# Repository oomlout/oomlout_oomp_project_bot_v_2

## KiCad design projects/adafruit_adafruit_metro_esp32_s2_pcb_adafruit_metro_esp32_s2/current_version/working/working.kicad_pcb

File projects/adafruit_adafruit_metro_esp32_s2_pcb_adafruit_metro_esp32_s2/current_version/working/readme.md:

# adafruit_metro_esp32_s2_pcb
 
## summary 
* id: adafruit_adafruit_metro_esp32_s2_pcb_adafruit_metro_esp32_s2
* user: adafruit
* name: adafruit_metro_esp32_s2_pcb
* board: adafruit_metro_esp32_s2
* repo: https://github.com/adafruit/Adafruit-Metro-ESP32-S2-PCB

* src_file_repo_sch: 
* src_file_repo_sch_link: https://github.com/adafruit/Adafruit-Metro-ESP32-S2-PCB/tree/master/
* full details link: https://github.com/oomlout/oomlout_oomp_project_bot_v_2/tree/main/projects/adafruit_adafruit_metro_esp32_s2_pcb_adafruit_metro_esp32_s2/current_version/working  

## schematic  
  
[schematic (pdf)](working_schematic.pdf) 

## pcb  

[board (pdf)](working.pdf)  

## working_bom
| Id | Designator | Footprint | Quantity | Designation | Supplier and ref |  | None | 
| --- | --- | --- | --- | --- | --- | --- | --- | 
| 1 | IOL0,POWER0 | 1X08_OVALWAVE | 2 | 20610 |  |  | [''] | 
| 2 | @HOLE3,@HOLE0,@HOLE2,@HOLE1 |  | 4 |  |  |  | [''] | 
| 3 | C4,C13,C7,C10,C18,C17,C11,C8 | 0805-NO | 8 | 10ÂµF |  |  | [''] | 
| 4 | C1,C3 | 0805-NO | 2 | 10uF |  |  | [''] | 
| 5 | U3 | MODULE_ESP32-S2-WROVER | 1 | ESP32-S2-WROVER |  |  | [''] | 
| 6 | D1,D4 | SOD-123 | 2 | MBR540 |  |  | [''] | 
| 7 | CHG1 | CHIPLED_0603_NOOUTLINE | 1 | ORANGE |  |  | [''] | 
| 8 | R15,R12,R16 | 0603-NO | 3 | 100K |  |  | [''] | 
| 9 | R2,R9,R6 | 0603-NO | 3 | 10K |  |  | [''] | 
| 10 | X5 | DCJACK_2MM_PTH | 1 | 2.1mm |  |  | [''] | 
| 11 | C5,C2,C12,C15 | 0603-NO | 4 | 0.1uF |  |  | [''] | 
| 12 | U$15 | PCBFEAT-REV-040 | 1 |  |  |  | [''] | 
| 13 | ON0 | CHIPLED_0603_NOOUTLINE | 1 | GREEN |  |  | [''] | 
| 14 | Q2,Q1 | SOT23-R | 2 | DMG3415U-7 |  |  | [''] | 
| 15 | X4 | USB_C_CUSB31-CFM2AX-01-X | 1 | USB C |  |  | [''] | 
| 16 | PC2 | PANASONIC_D | 1 | 47uF+/6.3V+ |  |  | [''] | 
| 17 | C14,C6 | 0603-NO | 2 | 1uF |  |  | [''] | 
| 18 | SW4 | SPDT_SMT_SSSS811101 | 1 | SPDT R/A |  |  | [''] | 
| 19 | SW1,SW3 | SPST_TACTILE_RA | 2 | RA_TACT |  |  | [''] | 
| 20 | FD2,FD1,FD3 | FIDUCIAL_1MM | 3 | FIDUCIAL_1MM |  |  | [''] | 
| 21 | LED1 | LED3535 | 1 | WS2812B3535 |  |  | [''] | 
| 22 | CONN1 | JST_SH4 | 1 | STEMMA_I2C_QT |  |  | [''] | 
| 23 | U1 | SOT223-R | 1 | NCP1117ST50T3G |  |  | [''] | 
| 24 | X1 | JSTPH2_BATT | 1 | JSTPH |  |  | [''] | 
| 25 | U$52 | ESP32S2_TOP | 1 |  |  |  | [''] | 
| 26 | U4 | SOT23-5 | 1 | AP2112(3.3V) |  |  | [''] | 
| 27 | IOH0 | 1X10_OVALWAVE | 1 | 20611 |  |  | [''] | 
| 28 | ICSP0 | 2X03_ROUND_70MIL | 1 | 3x2 M |  |  | [''] | 
| 29 | R14 | 0603-NO | 1 | 100k |  |  | [''] | 
| 30 | R3,R8 | 0603-NO | 2 | 5.1K |  |  | [''] | 
| 31 | X2 | 2X05_1.27MM_BOX_POSTS | 1 | 4u20317 |  |  | [''] | 
| 32 | U2 | SOT23-5 | 1 | MCP73831T-2ACI/OT |  |  | [''] | 
| 33 | L0 | CHIPLED_0603_NOOUTLINE | 1 | RED |  |  | [''] | 
| 34 | JP2 | 1X02_ROUND | 1 | UART |  |  | [''] | 
| 35 | PC1 | PANASONIC_D | 1 | 47uF/25V |  |  | [''] | 
| 36 | F2 | 1206 | 1 | 500mA |  |  | [''] | 
| 37 | R17 | 0603-NO | 1 | 1Meg |  |  | [''] | 
| 38 | R4 | 0603-NO | 1 | 2.2K |  |  | [''] | 
| 39 | AD0 | 1X06_OVALWAVE | 1 | 20609 |  |  | [''] | 
| 40 | R1 | RESPACK_4X0603 | 1 | 10K |  |  | [''] | 
| 41 | IC2 | WDFN8_3X4_0.65 | 1 | LC709203F |  |  | [''] | 
| 42 | U$53 | ESP32S2_BOT | 1 |  |  |  | [''] | 
| 43 | SJ1 | SOLDERJUMPER_CLOSEDWIRE | 1 |  |  |  | [''] | 
| 44 | TP1 | TESTPOINT_ROUND_1.5MM_NO | 1 |  |  |  | [''] | 

## bom_schematic
| Ref | Qnty | Value | Cmp name | Footprint | Description | Vendor | DNP | 
| --- | --- | --- | --- | --- | --- | --- | --- | 
| AD0 | 1 | 20609 | HEADER-1X6OVALWAVE | working:1X06_OVALWAVE |  |  |  | 
| C1, C3 | 2 | 10uF | CAP_CERAMIC0805-NOOUTLINE | working:0805-NO |  |  |  | 
| C2, C5, C12, C15 | 4 | 0.1uF | CAP_CERAMIC0603_NO | working:0603-NO |  |  |  | 
| C4, C7, C8, C10, C11, C13, C17, C18 | 8 | 10ÂµF | CAP_CERAMIC0805-NOOUTLINE | working:0805-NO |  |  |  | 
| C6, C14 | 2 | 1uF | CAP_CERAMIC0603_NO | working:0603-NO |  |  |  | 
| CHG1 | 1 | ORANGE | LED0603_NOOUTLINE | working:CHIPLED_0603_NOOUTLINE |  |  |  | 
| CONN1 | 1 | STEMMA_I2C_QT | STEMMA_I2C_QT | working:JST_SH4 |  |  |  | 
| D1, D4 | 2 | MBR540 | DIODE-SCHOTTKYSOD-123 | working:SOD-123 |  |  |  | 
| F2 | 1 | 500mA | PTC1206 | working:1206 |  |  |  | 
| FD1, FD2, FD3 | 3 | FIDUCIAL_1MM | FIDUCIAL_1MM | working:FIDUCIAL_1MM |  |  |  | 
| IC2 | 1 | LC709203F | LC709203F | working:WDFN8_3X4_0.65 |  |  |  | 
| ICSP0 | 1 | 3x2 M | HEADER-2X3 | working:2X03_ROUND_70MIL |  |  |  | 
| IOH0 | 1 | 20611 | HEADER-1X10OVALWAVE | working:1X10_OVALWAVE |  |  |  | 
| IOL0 | 1 | 20610 | HEADER-1X8OVALWAVE | working:1X08_OVALWAVE |  |  |  | 
| JP2 | 1 | UART | HEADER-1X2ROUND | working:1X02_ROUND |  |  |  | 
| L0 | 1 | RED | LED0603_NOOUTLINE | working:CHIPLED_0603_NOOUTLINE |  |  |  | 
| LED1 | 1 | WS2812B3535 | WS2812B3535 | working:LED3535 |  |  |  | 
| ON0 | 1 | GREEN | LED0603_NOOUTLINE | working:CHIPLED_0603_NOOUTLINE |  |  |  | 
| PC1 | 1 | 47uF/25V | CAP_ELECTROLYTICPANASONIC_D | working:PANASONIC_D |  |  |  | 
| PC2 | 1 | 47uF+/6.3V+ | CAP_ELECTROLYTICPANASONIC_D | working:PANASONIC_D |  |  |  | 
| POWER0 | 1 | 20610 | HEADER-1X8OVALWAVE | working:1X08_OVALWAVE |  |  |  | 
| Q1, Q2 | 2 | DMG3415U-7 | MOSFET-P | working:SOT23-R |  |  |  | 
| R1 | 1 | 10K | RESISTOR_4PACK | working:RESPACK_4X0603 |  |  |  | 
| R2, R6, R9 | 3 | 10K | RESISTOR_0603_NOOUT | working:0603-NO |  |  |  | 
| R3, R8 | 2 | 5.1K | RESISTOR_0603_NOOUT | working:0603-NO |  |  |  | 
| R4 | 1 | 2.2K | RESISTOR_0603_NOOUT | working:0603-NO |  |  |  | 
| R12, R15, R16 | 3 | 100K | RESISTOR_0603_NOOUT | working:0603-NO |  |  |  | 
| R14 | 1 | 100k | RESISTOR_0603_NOOUT | working:0603-NO |  |  |  | 
| R17 | 1 | 1Meg | RESISTOR_0603_NOOUT | working:0603-NO |  |  |  | 
| SJ1 | 1 | SOLDERJUMPER_CLOSED | SOLDERJUMPER_CLOSED | working:SOLDERJUMPER_CLOSEDWIRE |  |  |  | 
| SW1, SW3 | 2 | RA_TACT | SWITCH_SPST_TACT_RA | working:SPST_TACTILE_RA |  |  |  | 
| SW4 | 1 | SPDT R/A | SWITCH_SPDT | working:SPDT_SMT_SSSS811101 |  |  |  | 
| TP1 | 1 | TESTPOINTROUND1.5MMNO | TESTPOINTROUND1.5MMNO | working:TESTPOINT_ROUND_1.5MM_NO |  |  |  | 
| U1 | 1 | NCP1117ST50T3G | LM1117SOT223-REFLOW | working:SOT223-R |  |  |  | 
| U2 | 1 | MCP73831T-2ACI/OT | MCP73831/2 | working:SOT23-5 |  |  |  | 
| U3 | 1 | ESP32-S2-WROVER | ESP32-S2-WROVER | working:MODULE_ESP32-S2-WROVER |  |  |  | 
| U4 | 1 | AP2112(3.3V) | VREG_SOT23-5 | working:SOT23-5 |  |  |  | 
| X1 | 1 | JSTPH | CON_JST_PH_2PIN_BATT | working:JSTPH2_BATT |  |  |  | 
| X2 | 1 | 4u20317 | JTAG-CORTEXBOXPOSTS | working:2X05_1.27MM_BOX_POSTS |  |  |  | 
| X4 | 1 | USB C | USB_C | working:USB_C_CUSB31-CFM2AX-01-X |  |  |  | 
| X5 | 1 | 2.1mm | DCBARRELPTH | working:DCJACK_2MM_PTH |  |  |  |

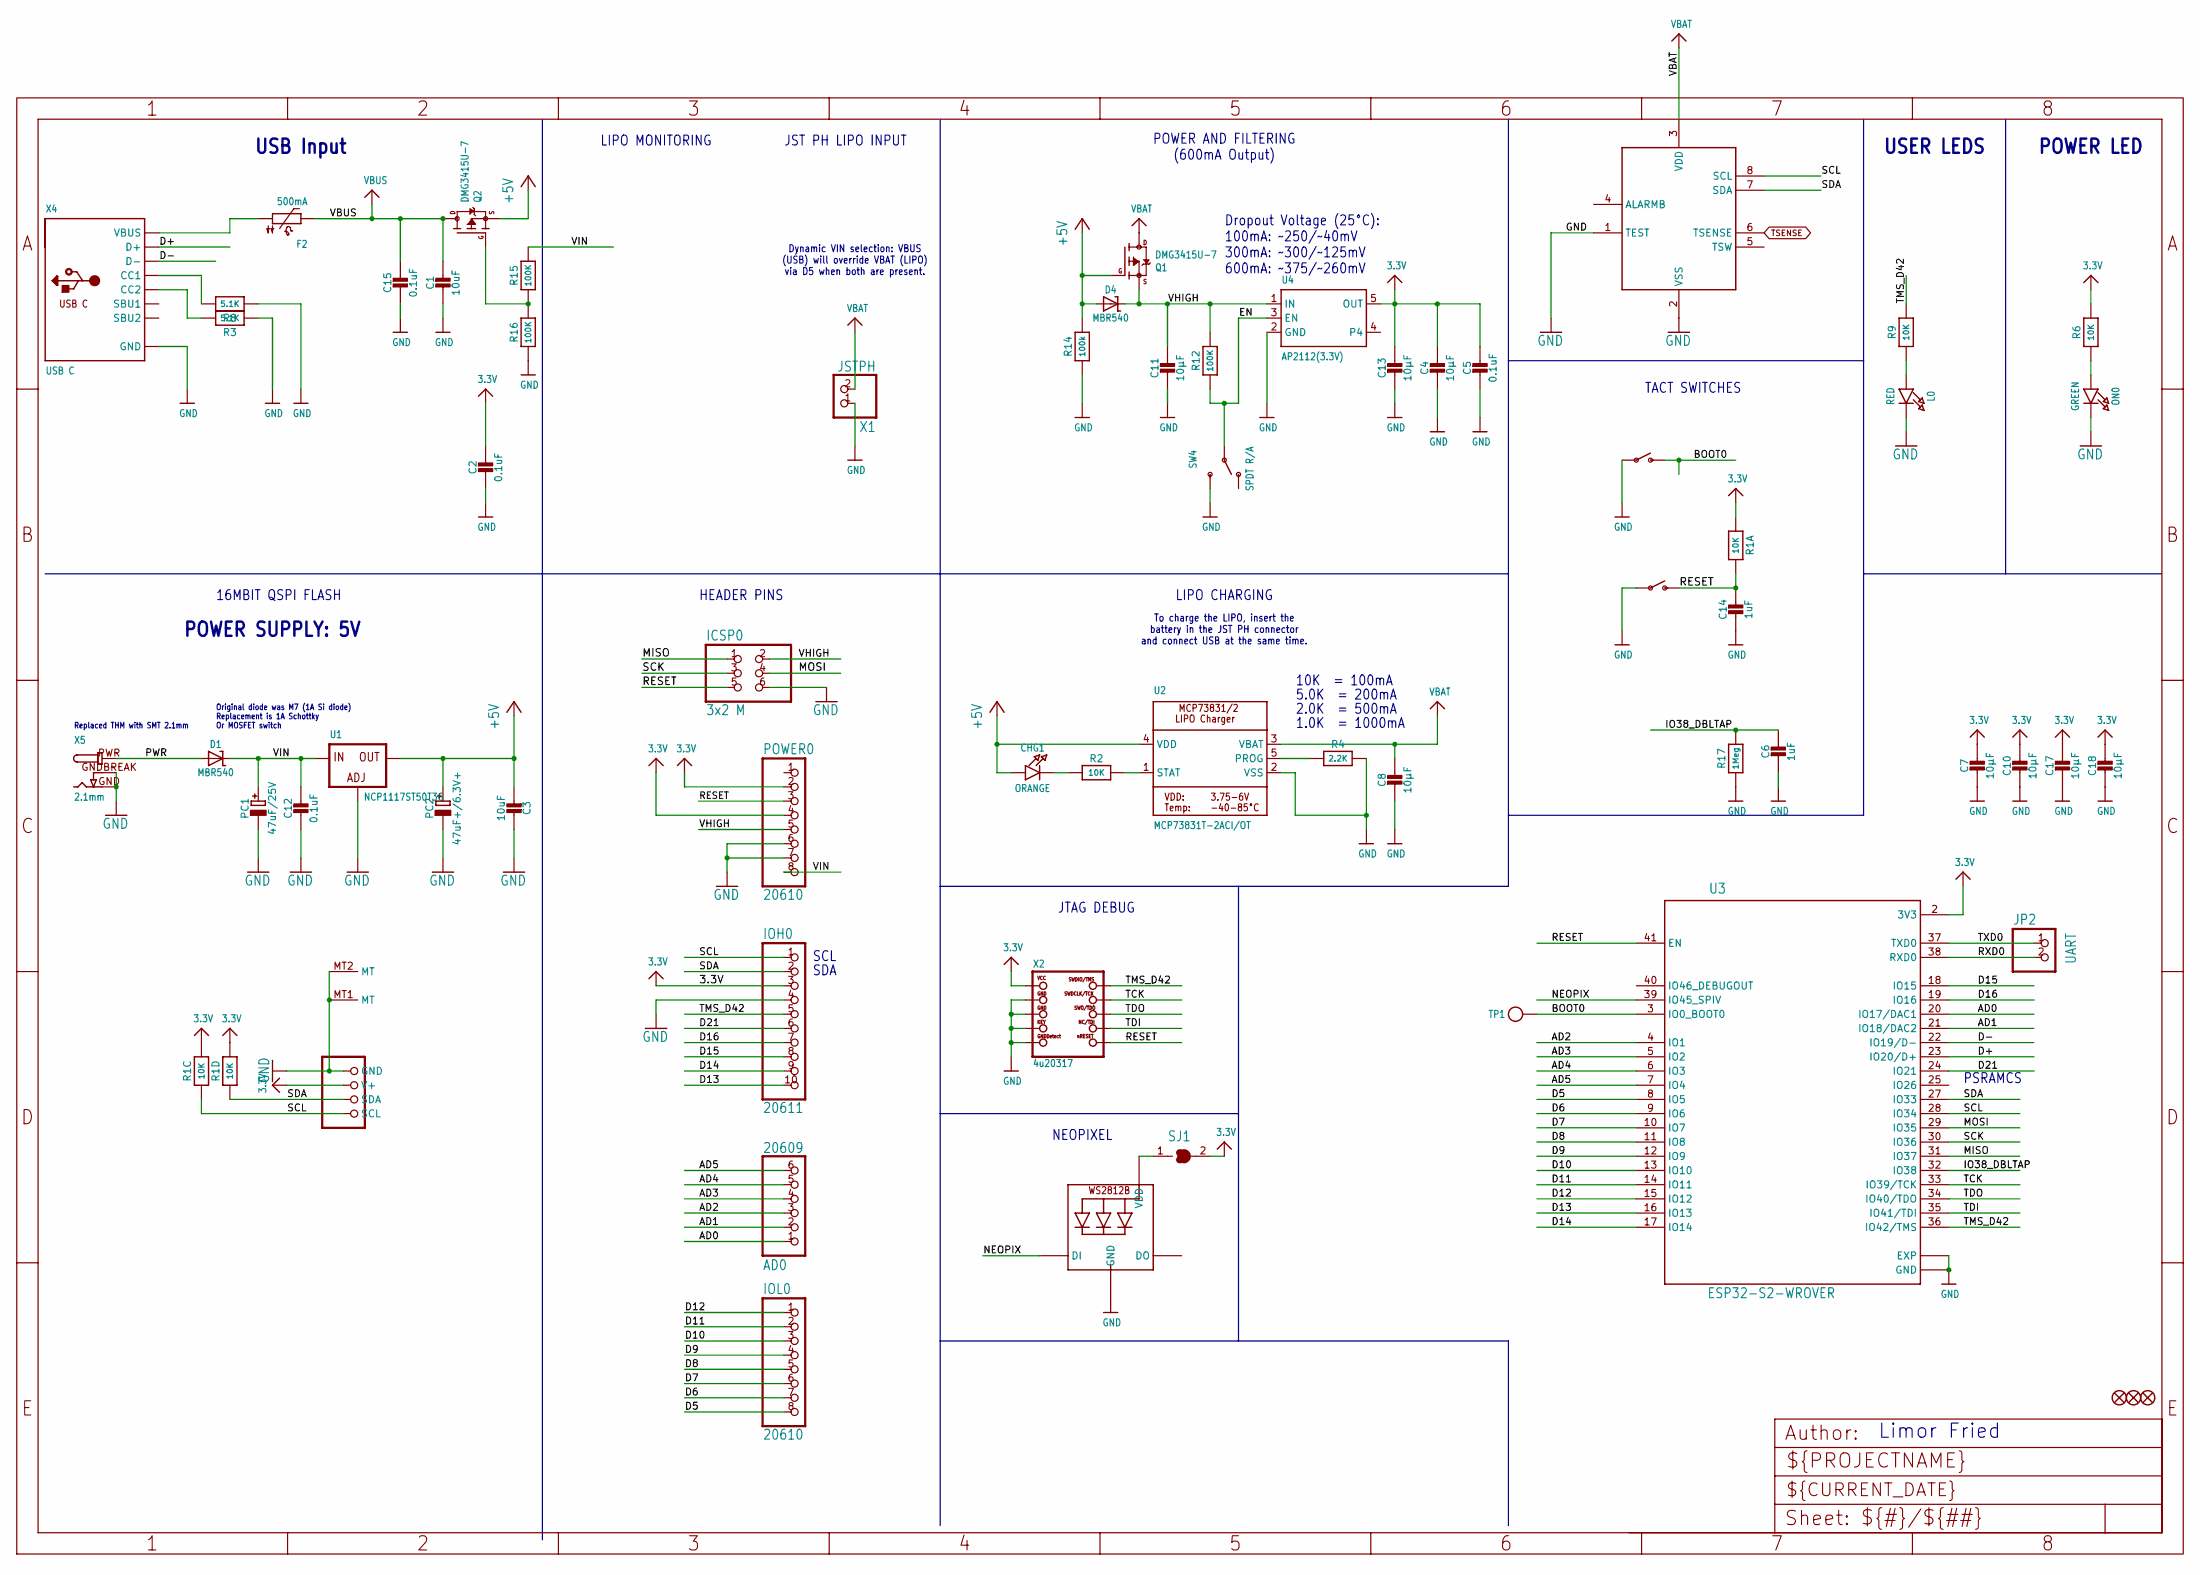
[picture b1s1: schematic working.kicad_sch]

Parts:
AD0: 20609; 1X06_OVALWAVE
C1, C3: 10uF; 0805-NO
C2, C5, C12, C15: 0.1uF; 0603-NO
C4, C7, C8, C10, C11, C13, C17, C18: 10µF; 0805-NO
C6, C14: 1uF; 0603-NO
CHG1: ORANGE; CHIPLED_0603_NOOUTLINE
CONN1: STEMMA_I2C_QT; JST_SH4
D1, D4: MBR540; SOD-123
F2: 500mA; 1206
FD1, FD2, FD3: FIDUCIAL_1MM
IC2: LC709203F; WDFN8_3X4_0.65
ICSP0: 3x2 M; 2X03_ROUND_70MIL
IOH0: 20611; 1X10_OVALWAVE
IOL0: 20610; 1X08_OVALWAVE
JP2: UART; 1X02_ROUND
L0: RED; CHIPLED_0603_NOOUTLINE
LED1: WS2812B3535; LED3535
ON0: GREEN; CHIPLED_0603_NOOUTLINE
PC1: 47uF/25V; PANASONIC_D
PC2: 47uF+/6.3V+; PANASONIC_D
POWER0: 20610; 1X08_OVALWAVE
Q1, Q2: DMG3415U-7; SOT23-R
R1: 10K; RESPACK_4X0603
R2, R6, R9: 10K; 0603-NO
R3, R8: 5.1K; 0603-NO
R4: 2.2K; 0603-NO
R12, R15, R16: 100K; 0603-NO
R14: 100k; 0603-NO
R17: 1Meg; 0603-NO
SJ1: SOLDERJUMPER_CLOSED; SOLDERJUMPER_CLOSEDWIRE
SW1, SW3: RA_TACT; SPST_TACTILE_RA
SW4: SPDT R/A; SPDT_SMT_SSSS811101
TP1: TESTPOINTROUND1.5MMNO; TESTPOINT_ROUND_1.5MM_NO
U1: NCP1117ST50T3G; SOT223-R
U2: MCP73831T-2ACI/OT; SOT23-5
U3: ESP32-S2-WROVER; MODULE_ESP32-S2-WROVER
U4: AP2112(3.3V); SOT23-5
X1: JSTPH; JSTPH2_BATT
X2: 4u20317; 2X05_1.27MM_BOX_POSTS
X4: USB C; USB_C_CUSB31-CFM2AX-01-X
X5: 2.1mm; DCJACK_2MM_PTH

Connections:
3.3V: C2.1, C4.1, C5.1, C7.1, C10.1, C13.1, C17.1, C18.1, CONN1.2 (V+), IOH0.3, POWER0.2, POWER0.4, R1.1, R1.5 (2), R1.6 (2), R6.2, SJ1.2, U3.2 (3V3), U4.5 (OUT), X2.1 (VCC)
+5V: C3.2, CHG1.A, D4.A, PC2.+, Q1.1 (G), Q2.2 (S), R14.2, U1.2 (OUT), U1.4 (OUT), U2.4 (VDD)
AD0: AD0.1, U3.20 (IO17/DAC1)
AD1: AD0.2, U3.21 (IO18/DAC2)
AD2: AD0.3, U3.4 (IO1)
AD3: AD0.4, U3.5 (IO2)
AD4: AD0.5, U3.6 (IO3)
AD5: AD0.6, U3.7 (IO4)
BOOT0: SW1.2 (S), TP1.P$1, U3.3 (IO0_BOOT0)
D5: IOL0.8, U3.8 (IO5)
D6: IOL0.7, U3.9 (IO6)
D7: IOL0.6, U3.10 (IO7)
D8: IOL0.5, U3.11 (IO8)
D9: IOL0.4, U3.12 (IO9)
D10: IOL0.3, U3.13 (IO10)
D11: IOL0.2, U3.14 (IO11)
D12: IOL0.1, U3.15 (IO12)
D13: IOH0.10, U3.16 (IO13)
D14: IOH0.9, U3.17 (IO14)
D15: IOH0.8, U3.18 (IO15)
D16: IOH0.7, U3.19 (IO16)
D21: IOH0.6, U3.24 (IO21)
D+: U3.23 (IO20/D+), X4.A6 (D+), X4.B6 (D+)
D-: U3.22 (IO19/D-), X4.A7 (D-), X4.B7 (D-)
EN: R12.1, SW4.B, U4.3 (EN)
GND: C1.2, C2.2, C3.1, C4.2, C5.2, C6.2, C7.2, C8.2, C10.2, C11.2, C12.2, C13.2, C14.2, C15.2, C17.2, C18.2, CONN1.1 (GND), CONN1.MT1 (MT), CONN1.MT2 (MT), IC2.1 (TEST), IC2.2 (VSS), ICSP0.6, IOH0.4, L0.C, LED1.4 (GND), ON0.C, PC1.-, PC2.-, POWER0.6, POWER0.7, R3.1, R4.2, R8.1, R14.1, R16.1, R17.1, SW1.1, SW3.1, SW4.C (S), U1.1 (ADJ), U2.2 (VSS), U3.1 (GND), U3.26 (GND), U3.42 (GND), U3.43_1 (EXP), U3.43_2 (EXP), U3.43_3 (EXP), U3.43_4 (EXP), U3.43_5 (EXP), U3.43_6 (EXP), U3.43_7 (EXP), U3.43_8 (EXP), U3.43_9 (EXP), U3.43_10 (EXP), U3.43_11 (EXP), U3.43_12 (EXP), U3.43_13 (EXP), U3.43_14 (EXP), U3.43_15 (EXP), U3.43_16 (EXP), U3.43_17 (EXP), U3.43_18 (EXP), U3.43_19 (EXP), U3.43_20 (EXP), U3.43_21 (EXP), U4.2 (GND), X1.1, X2.3 (GND@1), X2.5 (GND@2), X2.7 (KEY), X2.9 (GNDDETECT), X4.A1B12 (GND), X4.B1A12 (GND), X5.GND, X5.GNDBREAK
IO38_DBLTAP: C6.1, R17.2, U3.32 (IO38)
MISO: ICSP0.1, U3.31 (IO37)
MOSI: ICSP0.4, U3.29 (IO35)
unnamed: L0.A, R9.1
unnamed: Q2.1 (G), R15.1, R16.2
unnamed: ON0.A, R6.1
unnamed: CHG1.C, R2.1
unnamed: LED1.2 (VDD), SJ1.1
unnamed: R2.2, U2.1 (STAT)
unnamed: R8.2, X4.A5 (CC1)
unnamed: R3.2, X4.B5 (CC2)
unnamed: R4.1, U2.5 (PROG)
unnamed: F2.1, X4.A4B9 (VBUS), X4.B4A9 (VBUS)
NEOPIX: LED1.1 (DI), U3.39 (IO45_SPIV)
PWR: D1.A, X5.PWR
RESET: C14.1, ICSP0.5, POWER0.3, R1.8 (2), SW3.2 (S), U3.41 (EN), X2.10 (NRESET)
RXD0: JP2.2, U3.38 (RXD0)
SCK: ICSP0.3, U3.30 (IO36)
SCL: CONN1.4 (SCL), IC2.8 (SCL), IOH0.1, R1.3 (1), U3.28 (IO34)
SDA: CONN1.3 (SDA), IC2.7 (SDA), IOH0.2, R1.4 (1), U3.27 (IO33)
TCK: U3.33 (IO39/TCK), X2.4 (SWDCLK)
TDI: U3.35 (IO41/TDI), X2.8 (TDI)
TDO: U3.34 (IO40/TDO), X2.6 (SWO)
TMS_D42: IOH0.5, R9.2, U3.36 (IO42/TMS), X2.2 (SWDIO)
TXD0: JP2.1, U3.37 (TXD0)
VBAT: C8.1, IC2.3 (VDD), Q1.3 (D), U2.3 (VBAT), X1.2
VBUS: C1.1, C15.1, F2.2, Q2.3 (D)
VHIGH: C11.1, D4.C, ICSP0.2, POWER0.5, Q1.2 (S), R12.2, U4.1 (IN)
VIN: C12.1, D1.C, PC1.+, POWER0.8, R15.2, U1.3 (IN)

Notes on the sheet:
NEOPIXEL
POWER AND FILTERING (600mA Output)
5.0K = 200mA
SDA
16MBIT QSPI FLASH
2.0K = 500mA
LIPO MONITORING
Limor Fried
HEADER PINS
JTAG DEBUG
LIPO CHARGING
Dynamic VIN selection: VBUS (USB) will override VBAT (LIPO) via D5 when both are present.
JST PH LIPO INPUT
PSRAMCS
10K = 100mA
USB Input
To charge the LIPO, insert the battery in the JST PH connector and connect USB at the same time.
Replaced THM with SMT 2.1mm
POWER LED
USER LEDS
Original diode was M7 (1A Si diode) Replacement is 1A Schottky Or MOSFET switch
1.0K = 1000mA
POWER SUPPLY: 5V
TACT SWITCHES
Dropout Voltage (25°C): 100mA: ~250/~40mV 300mA: ~300/~125mV 600mA: ~375/~260mV
SCL

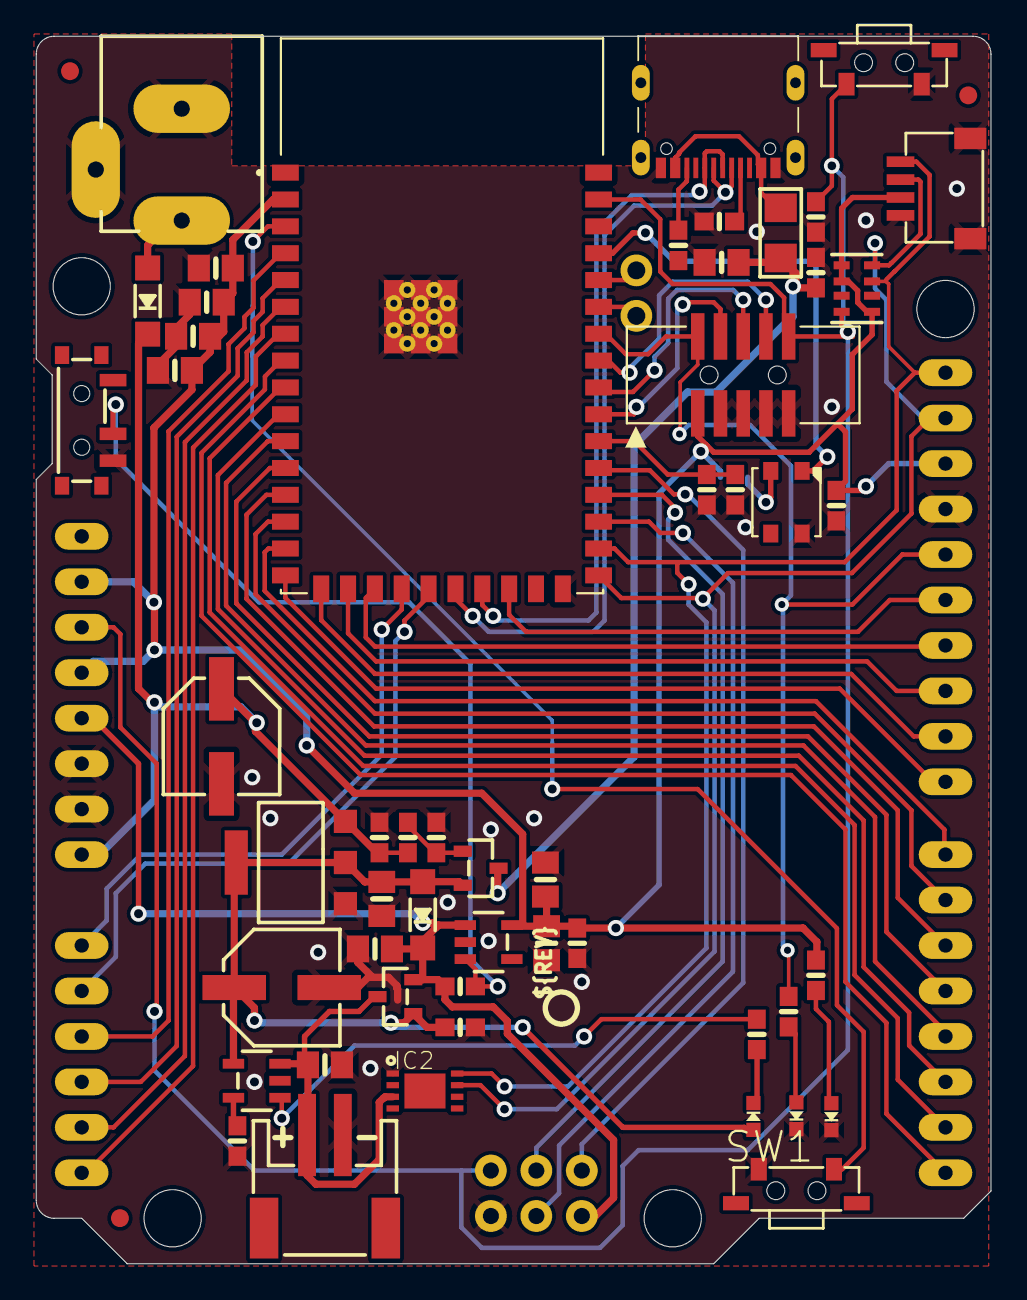
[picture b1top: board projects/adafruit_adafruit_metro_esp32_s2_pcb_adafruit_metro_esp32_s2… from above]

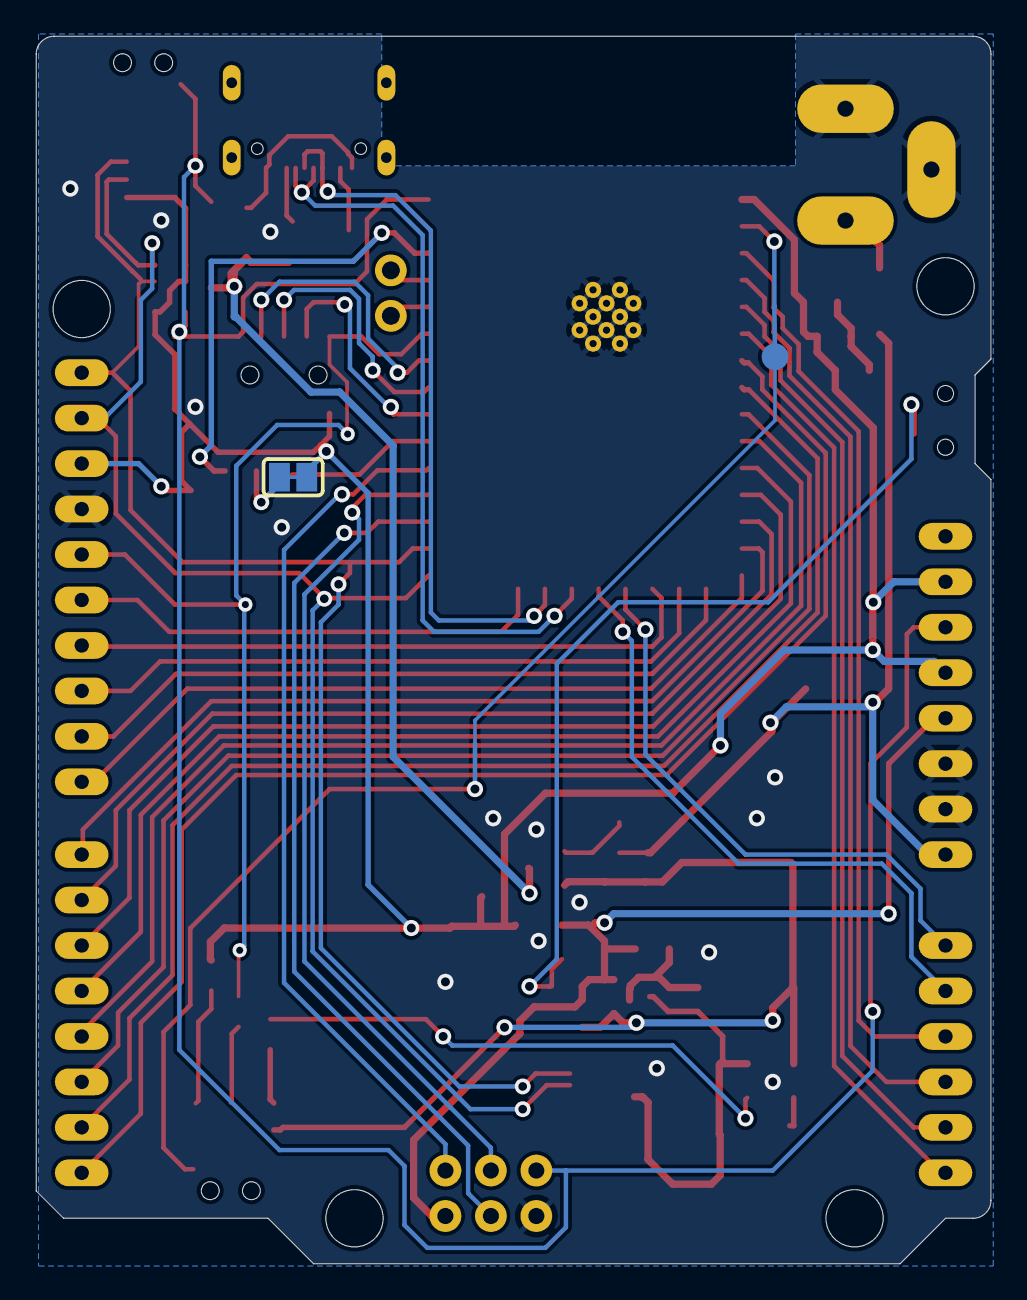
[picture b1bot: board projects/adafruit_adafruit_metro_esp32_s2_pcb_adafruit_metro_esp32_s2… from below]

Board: 2 copper layers, 53.3 x 68.6 mm, 70 parts (3 on the bottom side), 55 nets.

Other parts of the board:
@HOLE0, @HOLE1, @HOLE2, @HOLE3: (no value)
U$15: PCBFEAT-REV-040
U$52: ESP32S2_TOP
U$53: ESP32S2_BOT

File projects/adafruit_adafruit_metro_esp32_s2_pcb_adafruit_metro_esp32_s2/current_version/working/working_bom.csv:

"Id";"Designator";"Footprint";"Quantity";"Designation";"Supplier and ref";
1;"IOL0,POWER0";"1X08_OVALWAVE";2;"20610";;;
2;"@HOLE3,@HOLE0,@HOLE2,@HOLE1";"";4;"";;;
3;"C4,C13,C7,C10,C18,C17,C11,C8";"0805-NO";8;"10µF";;;
4;"C1,C3";"0805-NO";2;"10uF";;;
5;"U3";"MODULE_ESP32-S2-WROVER";1;"ESP32-S2-WROVER";;;
6;"D1,D4";"SOD-123";2;"MBR540";;;
7;"CHG1";"CHIPLED_0603_NOOUTLINE";1;"ORANGE";;;
8;"R15,R12,R16";"0603-NO";3;"100K";;;
9;"R2,R9,R6";"0603-NO";3;"10K";;;
10;"X5";"DCJACK_2MM_PTH";1;"2.1mm";;;
11;"C5,C2,C12,C15";"0603-NO";4;"0.1uF";;;
12;"U$15";"PCBFEAT-REV-040";1;"";;;
13;"ON0";"CHIPLED_0603_NOOUTLINE";1;"GREEN";;;
14;"Q2,Q1";"SOT23-R";2;"DMG3415U-7";;;
15;"X4";"USB_C_CUSB31-CFM2AX-01-X";1;"USB C";;;
16;"PC2";"PANASONIC_D";1;"47uF+/6.3V+";;;
17;"C14,C6";"0603-NO";2;"1uF";;;
18;"SW4";"SPDT_SMT_SSSS811101";1;"SPDT R/A";;;
19;"SW1,SW3";"SPST_TACTILE_RA";2;"RA_TACT";;;
20;"FD2,FD1,FD3";"FIDUCIAL_1MM";3;"FIDUCIAL_1MM";;;
21;"LED1";"LED3535";1;"WS2812B3535";;;
22;"CONN1";"JST_SH4";1;"STEMMA_I2C_QT";;;
23;"U1";"SOT223-R";1;"NCP1117ST50T3G";;;
24;"X1";"JSTPH2_BATT";1;"JSTPH";;;
25;"U$52";"ESP32S2_TOP";1;"";;;
26;"U4";"SOT23-5";1;"AP2112(3.3V)";;;
27;"IOH0";"1X10_OVALWAVE";1;"20611";;;
28;"ICSP0";"2X03_ROUND_70MIL";1;"3x2 M";;;
29;"R14";"0603-NO";1;"100k";;;
30;"R3,R8";"0603-NO";2;"5.1K";;;
31;"X2";"2X05_1.27MM_BOX_POSTS";1;"4u20317";;;
32;"U2";"SOT23-5";1;"MCP73831T-2ACI/OT";;;
33;"L0";"CHIPLED_0603_NOOUTLINE";1;"RED";;;
34;"JP2";"1X02_ROUND";1;"UART";;;
35;"PC1";"PANASONIC_D";1;"47uF/25V";;;
36;"F2";"1206";1;"500mA";;;
37;"R17";"0603-NO";1;"1Meg";;;
38;"R4";"0603-NO";1;"2.2K";;;
39;"AD0";"1X06_OVALWAVE";1;"20609";;;
40;"R1";"RESPACK_4X0603";1;"10K";;;
41;"IC2";"WDFN8_3X4_0.65";1;"LC709203F";;;
42;"U$53";"ESP32S2_BOT";1;"";;;
43;"SJ1";"SOLDERJUMPER_CLOSEDWIRE";1;"";;;
44;"TP1";"TESTPOINT_ROUND_1.5MM_NO";1;"";;;

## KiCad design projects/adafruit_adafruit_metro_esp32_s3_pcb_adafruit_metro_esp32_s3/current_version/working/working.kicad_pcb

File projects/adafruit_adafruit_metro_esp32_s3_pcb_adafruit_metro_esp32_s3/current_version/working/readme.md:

# adafruit_metro_esp32_s3_pcb
 
## summary 
* id: adafruit_adafruit_metro_esp32_s3_pcb_adafruit_metro_esp32_s3
* user: adafruit
* name: adafruit_metro_esp32_s3_pcb
* board: adafruit_metro_esp32_s3
* repo: https://github.com/adafruit/Adafruit-Metro-ESP32-S3-PCB

* src_file_repo_sch: 
* src_file_repo_sch_link: https://github.com/adafruit/Adafruit-Metro-ESP32-S3-PCB/tree/main/
* full details link: https://github.com/oomlout/oomlout_oomp_project_bot_v_2/tree/main/projects/adafruit_adafruit_metro_esp32_s3_pcb_adafruit_metro_esp32_s3/current_version/working  

## schematic  
  
[schematic (pdf)](working_schematic.pdf) 

## pcb  

[board (pdf)](working.pdf)  

## working_bom
| Id | Designator | Footprint | Quantity | Designation | Supplier and ref |  | None | 
| --- | --- | --- | --- | --- | --- | --- | --- | 
| 1 | Q2,Q1 | SOT23-R | 2 | DMG3415U-7 |  |  | [''] | 
| 2 | C15,C2,C12 | 0603-NO | 3 | 0.1uF |  |  | [''] | 
| 3 | R5,R6,R2,R7,R9,R1 | 0603-NO | 6 | 10K |  |  | [''] | 
| 4 | X3 | TDFN8_2X2MM | 1 | MAX17048/T |  |  | [''] | 
| 5 | C3,C17,C7,C13,C11,C4,C18,C10,C1,C8 | 0805-NO | 10 | 10uF |  |  | [''] | 
| 6 | X5 | DCJACK_2MM_PTH | 1 | 2.1mm |  |  | [''] | 
| 7 | SW1 | BTN_RKB2_4.6X2.8 | 1 | RKB2 |  |  | [''] | 
| 8 | U4 | SOT23-5 | 1 | AP2112(3.3V) |  |  | [''] | 
| 9 | @HOLE2,@HOLE0,@HOLE3,@HOLE1 |  | 4 |  |  |  | [''] | 
| 10 | JP2 | 1X02_ROUND | 1 | UART |  |  | [''] | 
| 11 | L0 | CHIPLED_0603_NOOUTLINE | 1 | RED |  |  | [''] | 
| 12 | SW4 | SPDT_SMT_SSSS811101 | 1 | SPDT R/A |  |  | [''] | 
| 13 | R17 | 0603-NO | 1 | 1Meg |  |  | [''] | 
| 14 | U2 | SOT23-5 | 1 | MCP73831T-2ACI/OT |  |  | [''] | 
| 15 | U1 | SOT223-R | 1 | NCP1117ST50T3G |  |  | [''] | 
| 16 | R12,R15,R16,R14 | 0603-NO | 4 | 100K |  |  | [''] | 
| 17 | ON0 | CHIPLED_0603_NOOUTLINE | 1 | GREEN |  |  | [''] | 
| 18 | U5 | S3-WROOM32 | 1 | ESP32-S3-WROOM |  |  | [''] | 
| 19 | R8,R3 | 0603-NO | 2 | 5.1K |  |  | [''] | 
| 20 | IOH0 | 1X10_OVALWAVE | 1 | 1x10 F |  |  | [''] | 
| 21 | R4 | 0603-NO | 1 | 2.2K |  |  | [''] | 
| 22 | FD1,FD2,FD3 | FIDUCIAL_1MM | 3 | FIDUCIAL_1MM |  |  | [''] | 
| 23 | X1 | JSTPH2_BATT | 1 | JSTPH |  |  | [''] | 
| 24 | CHG1 | CHIPLED_0603_NOOUTLINE | 1 | ORANGE |  |  | [''] | 
| 25 | PC2,PC1 | PANASONIC_D | 2 | 47uF/25V |  |  | [''] | 
| 26 | X6 | MOLEX_104031-0811 | 1 | MicroSD |  |  | [''] | 
| 27 | POWER0,IOL0 | 1X08_OVALWAVE | 2 | 1x8 F |  |  | [''] | 
| 28 | AD0 | 1X06_OVALWAVE | 1 | 1x6 F |  |  | [''] | 
| 29 | C14,C5,C6 | 0603-NO | 3 | 1uF |  |  | [''] | 
| 30 | SW3 | SPST_TACTILE_RA | 1 | RA_TACT |  |  | [''] | 
| 31 | CONN1 | JST_SH4 | 1 | STEMMA_I2C_QT |  |  | [''] | 
| 32 | F2 | 0805-NO | 1 | 500mA |  |  | [''] | 
| 33 | X2 | 2X05_1.27MM_BOX_POSTS | 1 | 2x5 0.05in |  |  | [''] | 
| 34 | D1,D4 | SOD-123 | 2 | MBR540 |  |  | [''] | 
| 35 | U$15 | PCBFEAT-REV-040 | 1 |  |  |  | [''] | 
| 36 | ICSP0 | 2X03_ROUND_70MIL | 1 | 3x2 M |  |  | [''] | 
| 37 | U$52 | METROS3_TOP | 1 |  |  |  | [''] | 
| 38 | X4 | USB_C_CUSB31-CFM2AX-01-X | 1 | USB C |  |  | [''] | 
| 39 | LED1 | LED3535_FULLPADS | 1 | WS2812B_3535FULL |  |  | [''] | 
| 40 | TP1 | TESTPOINT_ROUND_1.5MM_NO | 1 |  |  |  | [''] | 
| 41 | U$58 | METROS3_BOT | 1 |  |  |  | [''] | 
| 42 | SJ1 | SOLDERJUMPER_CLOSEDWIRE | 1 |  |  |  | [''] | 

## bom_schematic
| Ref | Qnty | Value | Cmp name | Footprint | Description | Vendor | DNP | 
| --- | --- | --- | --- | --- | --- | --- | --- | 
| AD0 | 1 | 1x6 F | HEADER-1X6OVALWAVE | working:1X06_OVALWAVE |  |  |  | 
| C1, C3, C4, C7, C8, C10, C11, C13, C17, C18 | 10 | 10uF | CAP_CERAMIC0805-NOOUTLINE | working:0805-NO |  |  |  | 
| C2, C12, C15 | 3 | 0.1uF | CAP_CERAMIC0603_NO | working:0603-NO |  |  |  | 
| C5, C6, C14 | 3 | 1uF | CAP_CERAMIC0603_NO | working:0603-NO |  |  |  | 
| CHG1 | 1 | ORANGE | LED0603_NOOUTLINE | working:CHIPLED_0603_NOOUTLINE |  |  |  | 
| CONN1 | 1 | STEMMA_I2C_QT | STEMMA_I2C_QT | working:JST_SH4 |  |  |  | 
| D1, D4 | 2 | MBR540 | DIODE-SCHOTTKYSOD-123 | working:SOD-123 |  |  |  | 
| F2 | 1 | 500mA | PTC_0805 | working:0805-NO |  |  |  | 
| FD1, FD2, FD3 | 3 | FIDUCIAL_1MM | FIDUCIAL_1MM | working:FIDUCIAL_1MM |  |  |  | 
| ICSP0 | 1 | 3x2 M | HEADER-2X3 | working:2X03_ROUND_70MIL |  |  |  | 
| IOH0 | 1 | 1x10 F | HEADER-1X10OVALWAVE | working:1X10_OVALWAVE |  |  |  | 
| IOL0 | 1 | 1x8 F | HEADER-1X8OVALWAVE | working:1X08_OVALWAVE |  |  |  | 
| JP2 | 1 | UART | HEADER-1X2ROUND | working:1X02_ROUND |  |  |  | 
| L0 | 1 | RED | LED0603_NOOUTLINE | working:CHIPLED_0603_NOOUTLINE |  |  |  | 
| LED1 | 1 | WS2812B_3535FULL | WS2812B_3535FULL | working:LED3535_FULLPADS |  |  |  | 
| ON0 | 1 | GREEN | LED0603_NOOUTLINE | working:CHIPLED_0603_NOOUTLINE |  |  |  | 
| PC1, PC2 | 2 | 47uF/25V | CAP_ELECTROLYTICPANASONIC_D | working:PANASONIC_D |  |  |  | 
| POWER0 | 1 | 1x8 F | HEADER-1X8OVALWAVE | working:1X08_OVALWAVE |  |  |  | 
| Q1, Q2 | 2 | DMG3415U-7 | MOSFET-P | working:SOT23-R |  |  |  | 
| R1, R2, R5, R6, R7, R9 | 6 | 10K | RESISTOR_0603_NOOUT | working:0603-NO |  |  |  | 
| R3, R8 | 2 | 5.1K | RESISTOR_0603_NOOUT | working:0603-NO |  |  |  | 
| R4 | 1 | 2.2K | RESISTOR_0603_NOOUT | working:0603-NO |  |  |  | 
| R12, R14, R15, R16 | 4 | 100K | RESISTOR_0603_NOOUT | working:0603-NO |  |  |  | 
| R17 | 1 | 1Meg | RESISTOR_0603_NOOUT | working:0603-NO |  |  |  | 
| SJ1 | 1 | SOLDERJUMPER_CLOSED | SOLDERJUMPER_CLOSED | working:SOLDERJUMPER_CLOSEDWIRE |  |  |  | 
| SW1 | 1 | RKB2 | SWITCH_TACT_SMT_RKB2 | working:BTN_RKB2_4.6X2.8 |  |  |  | 
| SW3 | 1 | RA_TACT | SWITCH_SPST_MNT_TACT_RA | working:SPST_TACTILE_RA |  |  |  | 
| SW4 | 1 | SPDT R/A | SWITCH_SPDT | working:SPDT_SMT_SSSS811101 |  |  |  | 
| TP1 | 1 | TESTPOINTROUND1.5MMNO | TESTPOINTROUND1.5MMNO | working:TESTPOINT_ROUND_1.5MM_NO |  |  |  | 
| U1 | 1 | NCP1117ST50T3G | LM1117SOT223-REFLOW | working:SOT223-R |  |  |  | 
| U2 | 1 | MCP73831T-2ACI/OT | MCP73831/2 | working:SOT23-5 |  |  |  | 
| U4 | 1 | AP2112(3.3V) | VREG_SOT23-5 | working:SOT23-5 |  |  |  | 
| U5 | 1 | ESP32-S3-WROOM | ESP32-S3-WROOM | working:S3-WROOM32 |  |  |  | 
| X1 | 1 | CON_JST_PH_2PIN_MT_BATT | CON_JST_PH_2PIN_MT_BATT | working:JSTPH2_BATT |  |  |  | 
| X2 | 1 | 2x5 0.05in | JTAG-CORTEXBOXPOSTS | working:2X05_1.27MM_BOX_POSTS |  |  |  | 
| X3 | 1 | MAX17048/T | MAX17048/T | working:TDFN8_2X2MM |  |  |  | 
| X4 | 1 | USB C | USB_C | working:USB_C_CUSB31-CFM2AX-01-X |  |  |  | 
| X5 | 1 | 2.1mm | DCBARRELPTH | working:DCJACK_2MM_PTH |  |  |  | 
| X6 | 1 | MicroSD | MICROSD104031-0811 | working:MOLEX_104031-0811 |  |  |  |

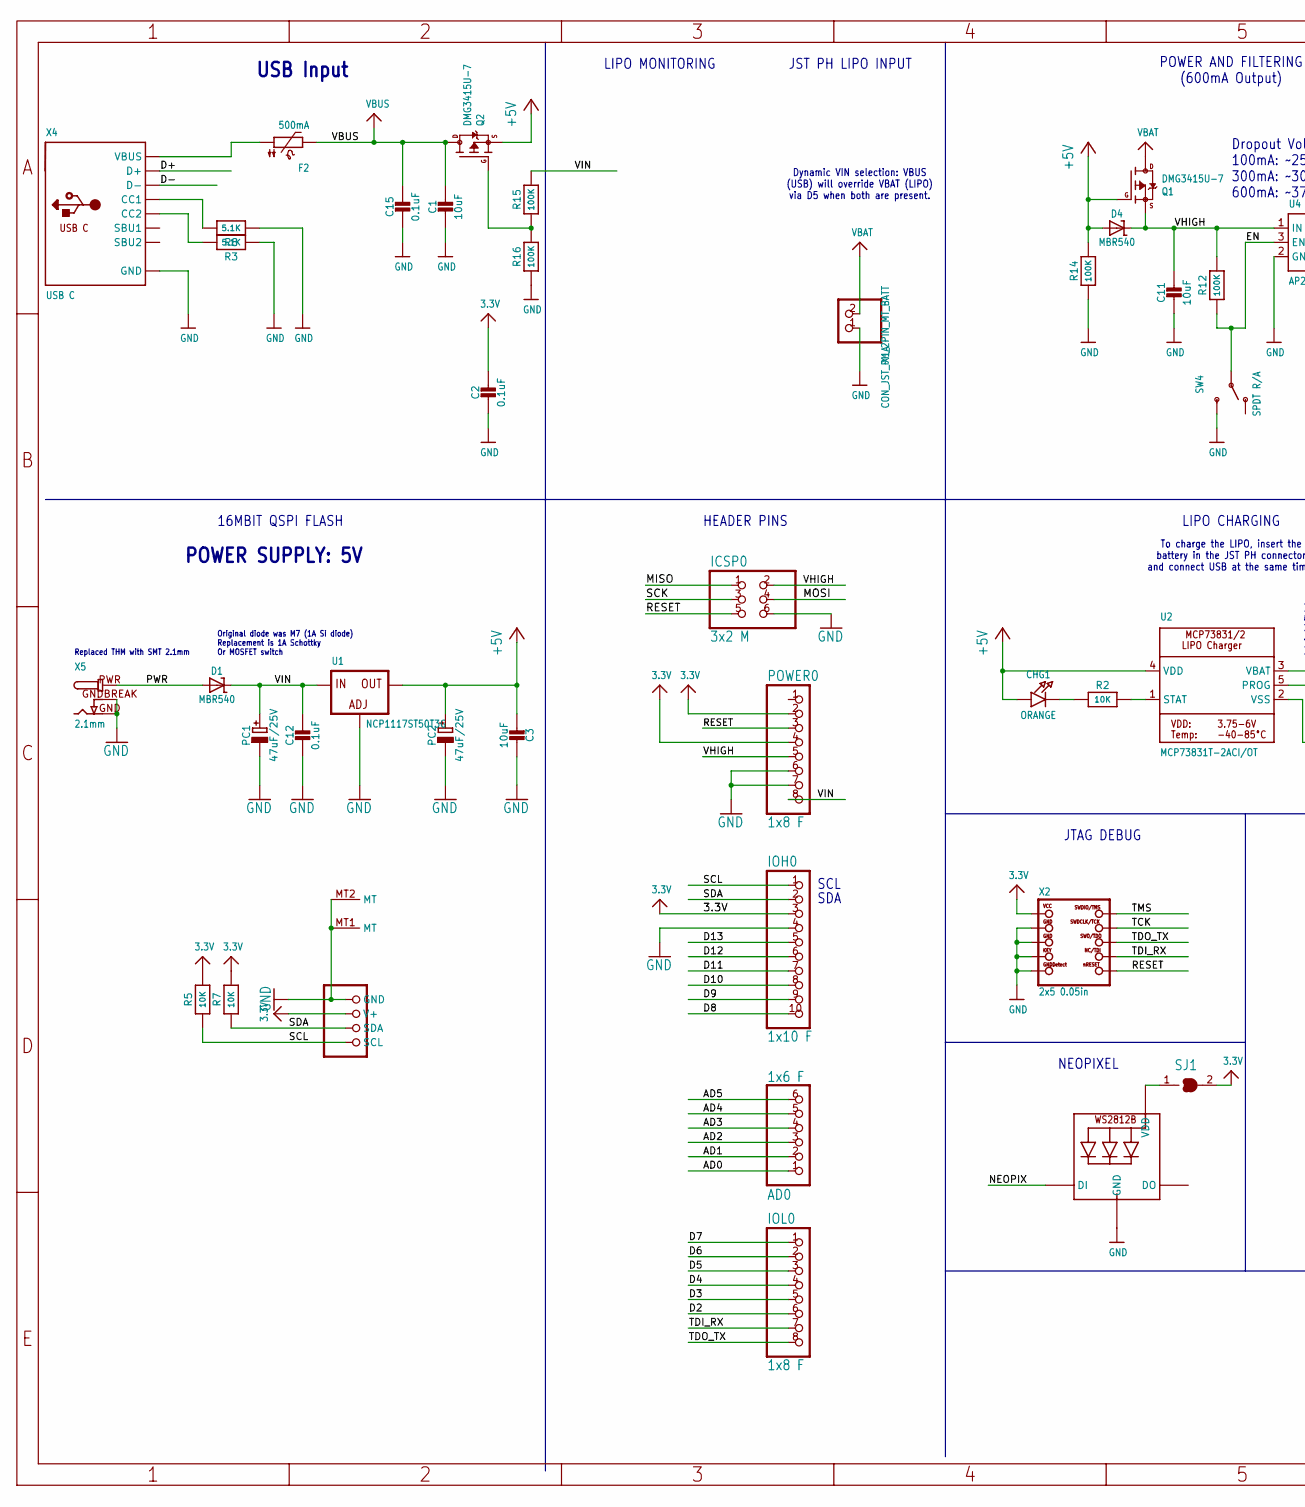
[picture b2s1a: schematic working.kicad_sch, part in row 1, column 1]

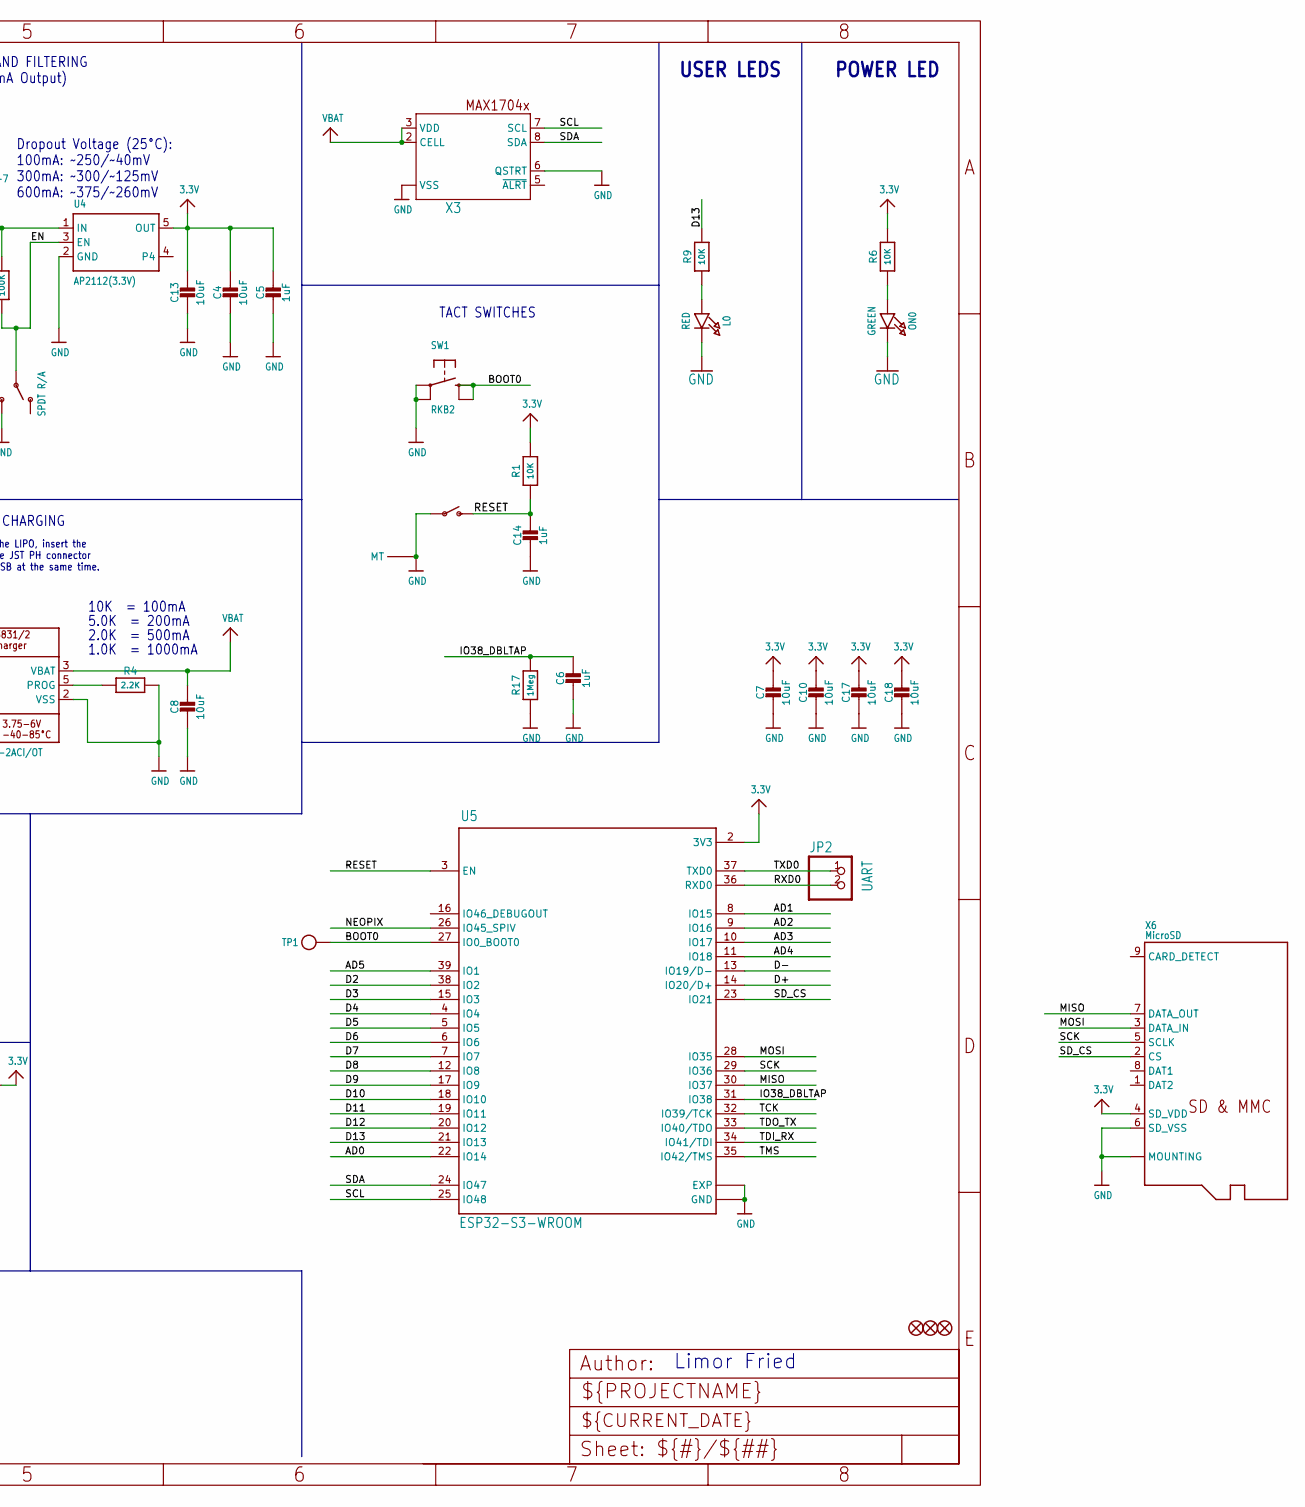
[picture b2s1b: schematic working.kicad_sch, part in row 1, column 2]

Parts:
AD0: 1x6 F; 1X06_OVALWAVE
C1, C3, C4, C7, C8, C10, C11, C13, C17, C18: 10uF; 0805-NO
C2, C12, C15: 0.1uF; 0603-NO
C5, C6, C14: 1uF; 0603-NO
CHG1: ORANGE; CHIPLED_0603_NOOUTLINE
CONN1: STEMMA_I2C_QT; JST_SH4
D1, D4: MBR540; SOD-123
F2: 500mA; 0805-NO
FD1, FD2, FD3: FIDUCIAL_1MM
ICSP0: 3x2 M; 2X03_ROUND_70MIL
IOH0: 1x10 F; 1X10_OVALWAVE
IOL0: 1x8 F; 1X08_OVALWAVE
JP2: UART; 1X02_ROUND
L0: RED; CHIPLED_0603_NOOUTLINE
LED1: WS2812B_3535FULL; LED3535_FULLPADS
ON0: GREEN; CHIPLED_0603_NOOUTLINE
PC1, PC2: 47uF/25V; PANASONIC_D
POWER0: 1x8 F; 1X08_OVALWAVE
Q1, Q2: DMG3415U-7; SOT23-R
R1, R2, R5, R6, R7, R9: 10K; 0603-NO
R3, R8: 5.1K; 0603-NO
R4: 2.2K; 0603-NO
R12, R14, R15, R16: 100K; 0603-NO
R17: 1Meg; 0603-NO
SJ1: SOLDERJUMPER_CLOSED; SOLDERJUMPER_CLOSEDWIRE
SW1: RKB2; BTN_RKB2_4.6X2.8
SW3: RA_TACT; SPST_TACTILE_RA
SW4: SPDT R/A; SPDT_SMT_SSSS811101
TP1: TESTPOINTROUND1.5MMNO; TESTPOINT_ROUND_1.5MM_NO
U1: NCP1117ST50T3G; SOT223-R
U2: MCP73831T-2ACI/OT; SOT23-5
U4: AP2112(3.3V); SOT23-5; JLC_ROTATION 0
U5: ESP32-S3-WROOM; S3-WROOM32
X1: CON_JST_PH_2PIN_MT_BATT; JSTPH2_BATT
X2: 2x5 0.05in; 2X05_1.27MM_BOX_POSTS
X3: MAX17048/T; TDFN8_2X2MM
X4: USB C; USB_C_CUSB31-CFM2AX-01-X
X5: 2.1mm; DCJACK_2MM_PTH
X6: MicroSD; MOLEX_104031-0811

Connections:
3.3V: C2.1, C4.1, C5.1, C7.1, C10.1, C13.1, C17.1, C18.1, CONN1.2 (V+), IOH0.3, POWER0.2, POWER0.4, R1.2, R5.2, R6.2, R7.2, SJ1.2, U4.5 (OUT), U5.2 (3V3), X2.1 (VCC), X6.4 (SD_VDD)
+5V: C3.2, CHG1.A, D4.A, PC2.+, Q1.1 (G), Q2.2 (S), R14.2, U1.2 (OUT), U1.4 (OUT), U2.4 (VDD)
AD0: AD0.1, U5.22 (IO14)
AD1: AD0.2, U5.8 (IO15)
AD2: AD0.3, U5.9 (IO16)
AD3: AD0.4, U5.10 (IO17)
AD4: AD0.5, U5.11 (IO18)
AD5: AD0.6, U5.39 (IO1)
BOOT0: SW1.B (S), SW1.B' (S1), TP1.P$1, U5.27 (IO0_BOOT0)
D2: IOL0.6, U5.38 (IO2)
D3: IOL0.5, U5.15 (IO3)
D4: IOL0.4, U5.4 (IO4)
D5: IOL0.3, U5.5 (IO5)
D6: IOL0.2, U5.6 (IO6)
D7: IOL0.1, U5.7 (IO7)
D8: IOH0.10, U5.12 (IO8)
D9: IOH0.9, U5.17 (IO9)
D10: IOH0.8, U5.18 (IO10)
D11: IOH0.7, U5.19 (IO11)
D12: IOH0.6, U5.20 (IO12)
D13: IOH0.5, R9.2, U5.21 (IO13)
D+: U5.14 (IO20/D+), X4.A6 (D+), X4.B6 (D+)
D-: U5.13 (IO19/D-), X4.A7 (D-), X4.B7 (D-)
EN: R12.1, SW4.B, U4.3 (EN)
GND: C1.2, C2.2, C3.1, C4.2, C5.2, C6.2, C7.2, C8.2, C10.2, C11.2, C12.2, C13.2, C14.2, C15.2, C17.2, C18.2, CONN1.1 (GND), CONN1.MT1 (MT), CONN1.MT2 (MT), ICSP0.6, IOH0.4, L0.C, LED1.4 (GND), ON0.C, PC1.-, PC2.-, POWER0.6, POWER0.7, R3.1, R4.2, R8.1, R14.1, R16.1, R17.1, SW1.A, SW1.A' (P1), SW3.1, SW3.MT1 (MT), SW3.MT2 (MT), SW4.C (S), U1.1 (ADJ), U2.2 (VSS), U4.2 (GND), U5.1 (GND), U5.40 (GND), U5.P$2 (EXP), U5.P$3 (EXP), U5.P$4 (EXP), U5.P$5 (EXP), U5.P$6 (EXP), U5.P$7 (EXP), U5.P$8 (EXP), U5.P$9 (EXP), U5.P$10 (EXP), X1.1, X2.3 (GND@1), X2.5 (GND@2), X2.7 (KEY), X2.9 (GNDDETECT), X3.1 (VSS), X3.4 (VSS), X3.6 (QSTRT), X3.THERMAL (VSS), X4.A1B12 (GND), X4.B1A12 (GND), X5.GND, X5.GNDBREAK, X6.6 (SD_VSS), X6.10 (MOUNTING), X6.G1 (MOUNTING), X6.G2 (MOUNTING), X6.G3 (MOUNTING), X6.G4 (MOUNTING)
IO38_DBLTAP: C6.1, R17.2, U5.31 (IO38)
MISO: ICSP0.1, U5.30 (IO37), X6.7 (DATA_OUT)
MOSI: ICSP0.4, U5.28 (IO35), X6.3 (DATA_IN)
unnamed: L0.A, R9.1
unnamed: Q2.1 (G), R15.1, R16.2
unnamed: ON0.A, R6.1
unnamed: CHG1.C, R2.1
unnamed: LED1.2 (VDD), SJ1.1
unnamed: R2.2, U2.1 (STAT)
unnamed: R8.2, X4.A5 (CC1)
unnamed: R3.2, X4.B5 (CC2)
unnamed: R4.1, U2.5 (PROG)
unnamed: F2.1, X4.A4B9 (VBUS), X4.B4A9 (VBUS)
NEOPIX: LED1.1 (DI), U5.26 (IO45_SPIV)
PWR: D1.A, X5.PWR
RESET: C14.1, ICSP0.5, POWER0.3, R1.1, SW3.2 (S), U5.3 (EN), X2.10 (NRESET)
RXD0: JP2.2, U5.36 (RXD0)
SCK: ICSP0.3, U5.29 (IO36), X6.5 (SCLK)
SCL: CONN1.4 (SCL), IOH0.1, R5.1, U5.25 (IO48), X3.7 (SCL)
SDA: CONN1.3 (SDA), IOH0.2, R7.1, U5.24 (IO47), X3.8 (SDA)
SD_CS: U5.23 (IO21), X6.2 (CS)
TCK: U5.32 (IO39/TCK), X2.4 (SWDCLK)
TDI_RX: IOL0.7, U5.34 (IO41/TDI), X2.8 (TDI)
TDO_TX: IOL0.8, U5.33 (IO40/TDO), X2.6 (SWO)
TMS: U5.35 (IO42/TMS), X2.2 (SWDIO)
TXD0: JP2.1, U5.37 (TXD0)
VBAT: C8.1, Q1.3 (D), U2.3 (VBAT), X1.2, X3.2 (CELL), X3.3 (VDD)
VBUS: C1.1, C15.1, F2.2, Q2.3 (D)
VHIGH: C11.1, D4.C, ICSP0.2, POWER0.5, Q1.2 (S), R12.2, U4.1 (IN)
VIN: C12.1, D1.C, PC1.+, POWER0.8, R15.2, U1.3 (IN)

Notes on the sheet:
Replaced THM with SMT 2.1mm
Original diode was M7 (1A Si diode) Replacement is 1A Schottky Or MOSFET switch
2.0K = 500mA
16MBIT QSPI FLASH
SCL
LIPO MONITORING
POWER LED
SDA
Dynamic VIN selection: VBUS (USB) will override VBAT (LIPO) via D5 when both are present.
To charge the LIPO, insert the battery in the JST PH connector and connect USB at the same time.
POWER AND FILTERING (600mA Output)
JST PH LIPO INPUT
NEOPIXEL
USB Input
POWER SUPPLY: 5V
HEADER PINS
Limor Fried
1.0K = 1000mA
LIPO CHARGING
10K = 100mA
5.0K = 200mA
JTAG DEBUG
TACT SWITCHES
USER LEDS
Dropout Voltage (25°C): 100mA: ~250/~40mV 300mA: ~300/~125mV 600mA: ~375/~260mV
